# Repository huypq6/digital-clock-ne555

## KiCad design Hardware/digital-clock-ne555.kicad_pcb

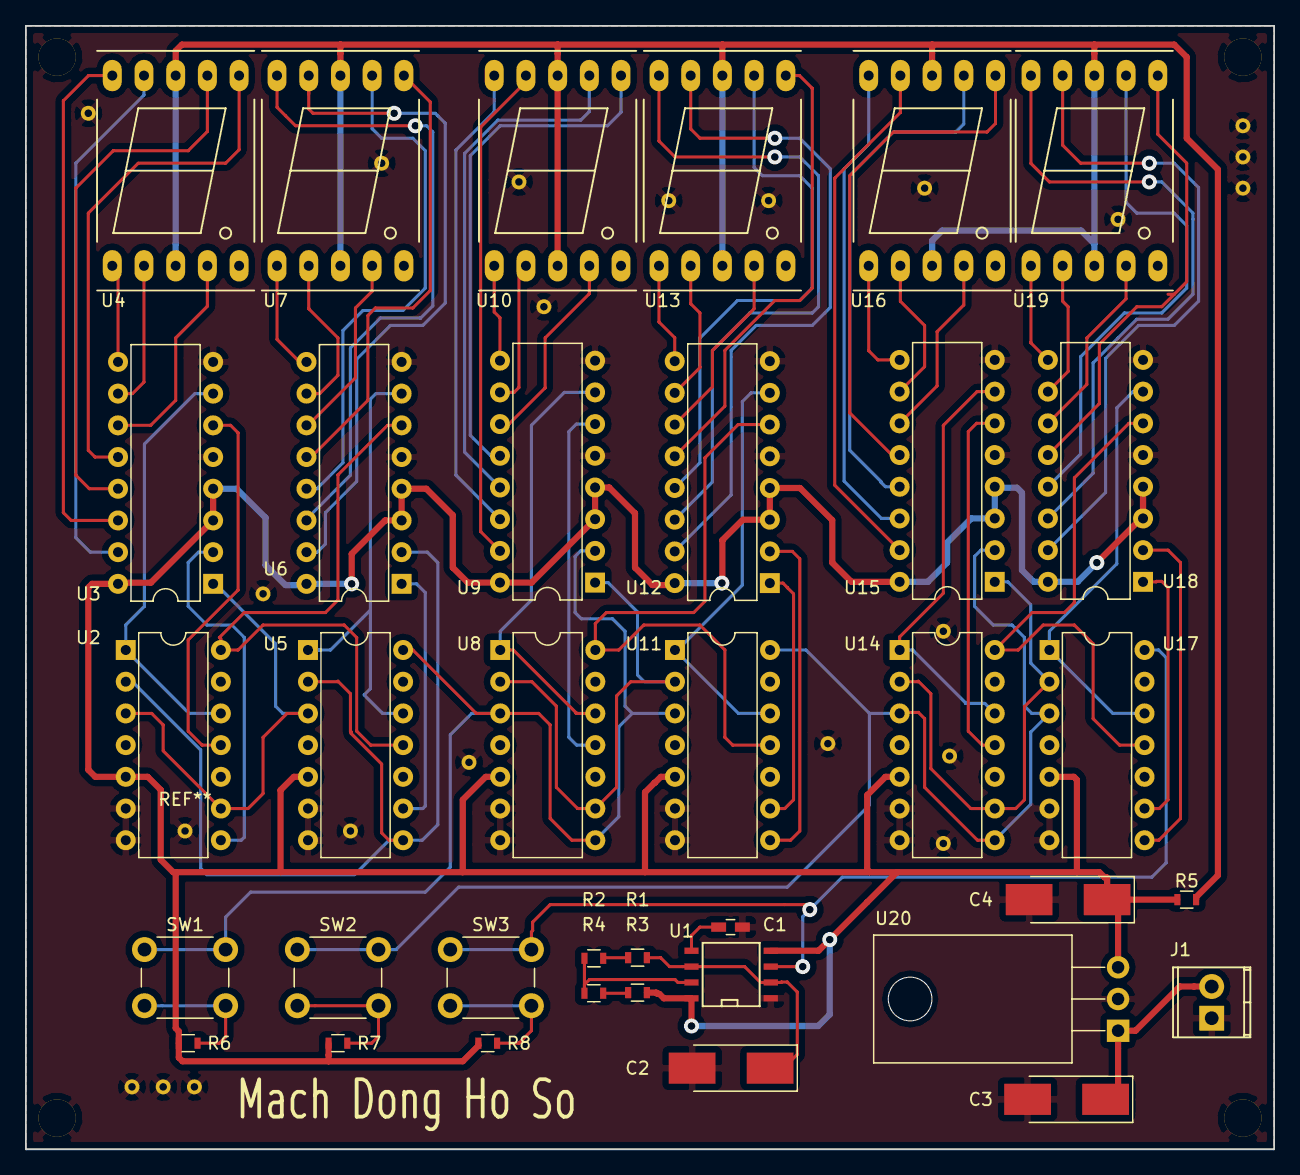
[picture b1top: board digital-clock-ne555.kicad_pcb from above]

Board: 2 copper layers, 100.0 x 90.0 mm, 36 parts (0 on the bottom side), 79 nets.

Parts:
C1: C; C_0603_HandSoldering
C2, C3, C4: CP; CP_Tantalum_Case-C_EIA-6032-28_Hand
J1: CONN_01X02; TerminalBlock_Pheonix_MPT-2.54mm_2pol
R1, R4: 1K; R_0603
R2, R3: 3K9; R_0603
R5: 330R; R_0603
R6, R7, R8: 10K; R_0603
SW1, SW2, SW3: SW_Push; SW_PUSH_6mm
U1: NE555; SOIC-8-N
U2, U5, U8, U11, U14, U17: 74LS90; DIP-14_W7.62mm
U3, U6, U9, U12, U15, U18: 74LS47; DIP-16_W7.62mm
U4, U7, U10, U13, U16, U19: 7SEGMENT_CA; 7SegmentLED_LTS6760_LTS6780
U20: LM7805; TO-220_Horizontal

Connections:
/Clock-1HZ: SW3.1, U1.3, U17.14
/Net1: U2.1, U2.12, U3.7
/Net2: U2.3, U2.9, U3.1, U5.3
/Net3: U2.8, U3.2
/Net4: U2.11, U3.6
/Net5: U5.1, U5.12, U6.7
/Net6: U5.9, U6.1
/Net7: U2.2, U5.2, U5.8, U6.2
/Net8: U2.14, U5.11, U6.6
/Net9: U8.1, U8.12, U9.7
/Net10: U8.2, U8.9, U9.1, U11.2
/Net11: SW1.1, U5.14, U8.3, U8.8, U9.2, U11.3
/Net12: U8.11, U9.6
/Net13: U11.1, U11.12, U12.7
/Net14: U11.9, U12.1
/Net15: U11.8, U12.2
/Net16: U8.14, U11.11, U12.6
/Net17: U14.1, U14.12, U15.7
/Net18: U14.2, U14.9, U15.1, U17.2
/Net19: SW2.1, U11.14, U14.3, U14.8, U15.2, U17.3
/Net20: U14.11, U15.6
/Net21: U17.1, U17.12, U18.7
/Net22: U17.9, U18.1
/Net23: U17.8, U18.2
/Net24: U14.14, U17.11, U18.6
GND: C1.2, C2.2, C3.2, C4.2, J1.1, U1.1, U2.6, U2.7, U3.5, U3.8, U5.6, U5.7, U6.5, U6.8, U8.6, U8.7, U9.5, U9.8, U11.6, U11.7, U12.5, U12.8, U14.6, U14.7, U15.5, U15.8, U17.6, U17.7, U18.5, U18.8, U20.2
unnamed: C1.1, U1.5
unnamed: C2.1, R1.2, U1.2, U1.6
unnamed: C3.1, J1.2, U20.1
unnamed: R1.1, R2.1
unnamed: R2.2, R4.2, U1.7
unnamed: R3.2, R4.1
unnamed: R5.1, U4.3, U4.8, U7.3, U7.8, U10.3, U10.8, U13.3, U13.8, U16.3, U16.8, U19.3, U19.8
unnamed: R6.2, SW1.2
unnamed: R7.2, SW2.2
unnamed: R8.2, SW3.2
unnamed: U3.9, U4.1
unnamed: U3.10, U4.2
unnamed: U3.11, U4.4
unnamed: U3.12, U4.6
unnamed: U3.13, U4.7
unnamed: U3.14, U4.10
unnamed: U3.15, U4.9
unnamed: U6.9, U7.1
unnamed: U6.10, U7.2
unnamed: U6.11, U7.4
unnamed: U6.12, U7.6
unnamed: U6.13, U7.7
unnamed: U6.14, U7.10
unnamed: U6.15, U7.9
unnamed: U9.9, U10.1
unnamed: U9.10, U10.2
unnamed: U9.11, U10.4
unnamed: U9.12, U10.6
unnamed: U9.13, U10.7
unnamed: U9.15, U10.9
unnamed: U9.14, U10.10
unnamed: U12.9, U13.1
unnamed: U12.10, U13.2
unnamed: U12.11, U13.4
unnamed: U12.12, U13.6
unnamed: U12.13, U13.7
unnamed: U12.14, U13.10
unnamed: U12.15, U13.9
unnamed: U15.9, U16.1
unnamed: U15.10, U16.2
unnamed: U15.11, U16.4
unnamed: U15.12, U16.6
unnamed: U15.13, U16.7
unnamed: U15.14, U16.10
unnamed: U15.15, U16.9
unnamed: U18.9, U19.1
unnamed: U18.10, U19.2
unnamed: U18.11, U19.4
unnamed: U18.12, U19.6
unnamed: U18.13, U19.7
unnamed: U18.14, U19.10
unnamed: U18.15, U19.9
VCC: C4.1, R3.1, R5.2, R6.1, R7.1, R8.1, U1.4, U1.8, U2.5, U3.3, U3.4, U3.16, U5.5, U6.3, U6.4, U6.16, U8.5, U9.3, U9.4, U9.16, U11.5, U12.3, U12.4, U12.16, U14.5, U15.3, U15.4, U15.16, U17.5, U18.3, U18.4, U18.16, U20.3

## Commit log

2017-05-30 add netlist
2017-05-30 Digital Clock
2017-05-30 unrouted net
